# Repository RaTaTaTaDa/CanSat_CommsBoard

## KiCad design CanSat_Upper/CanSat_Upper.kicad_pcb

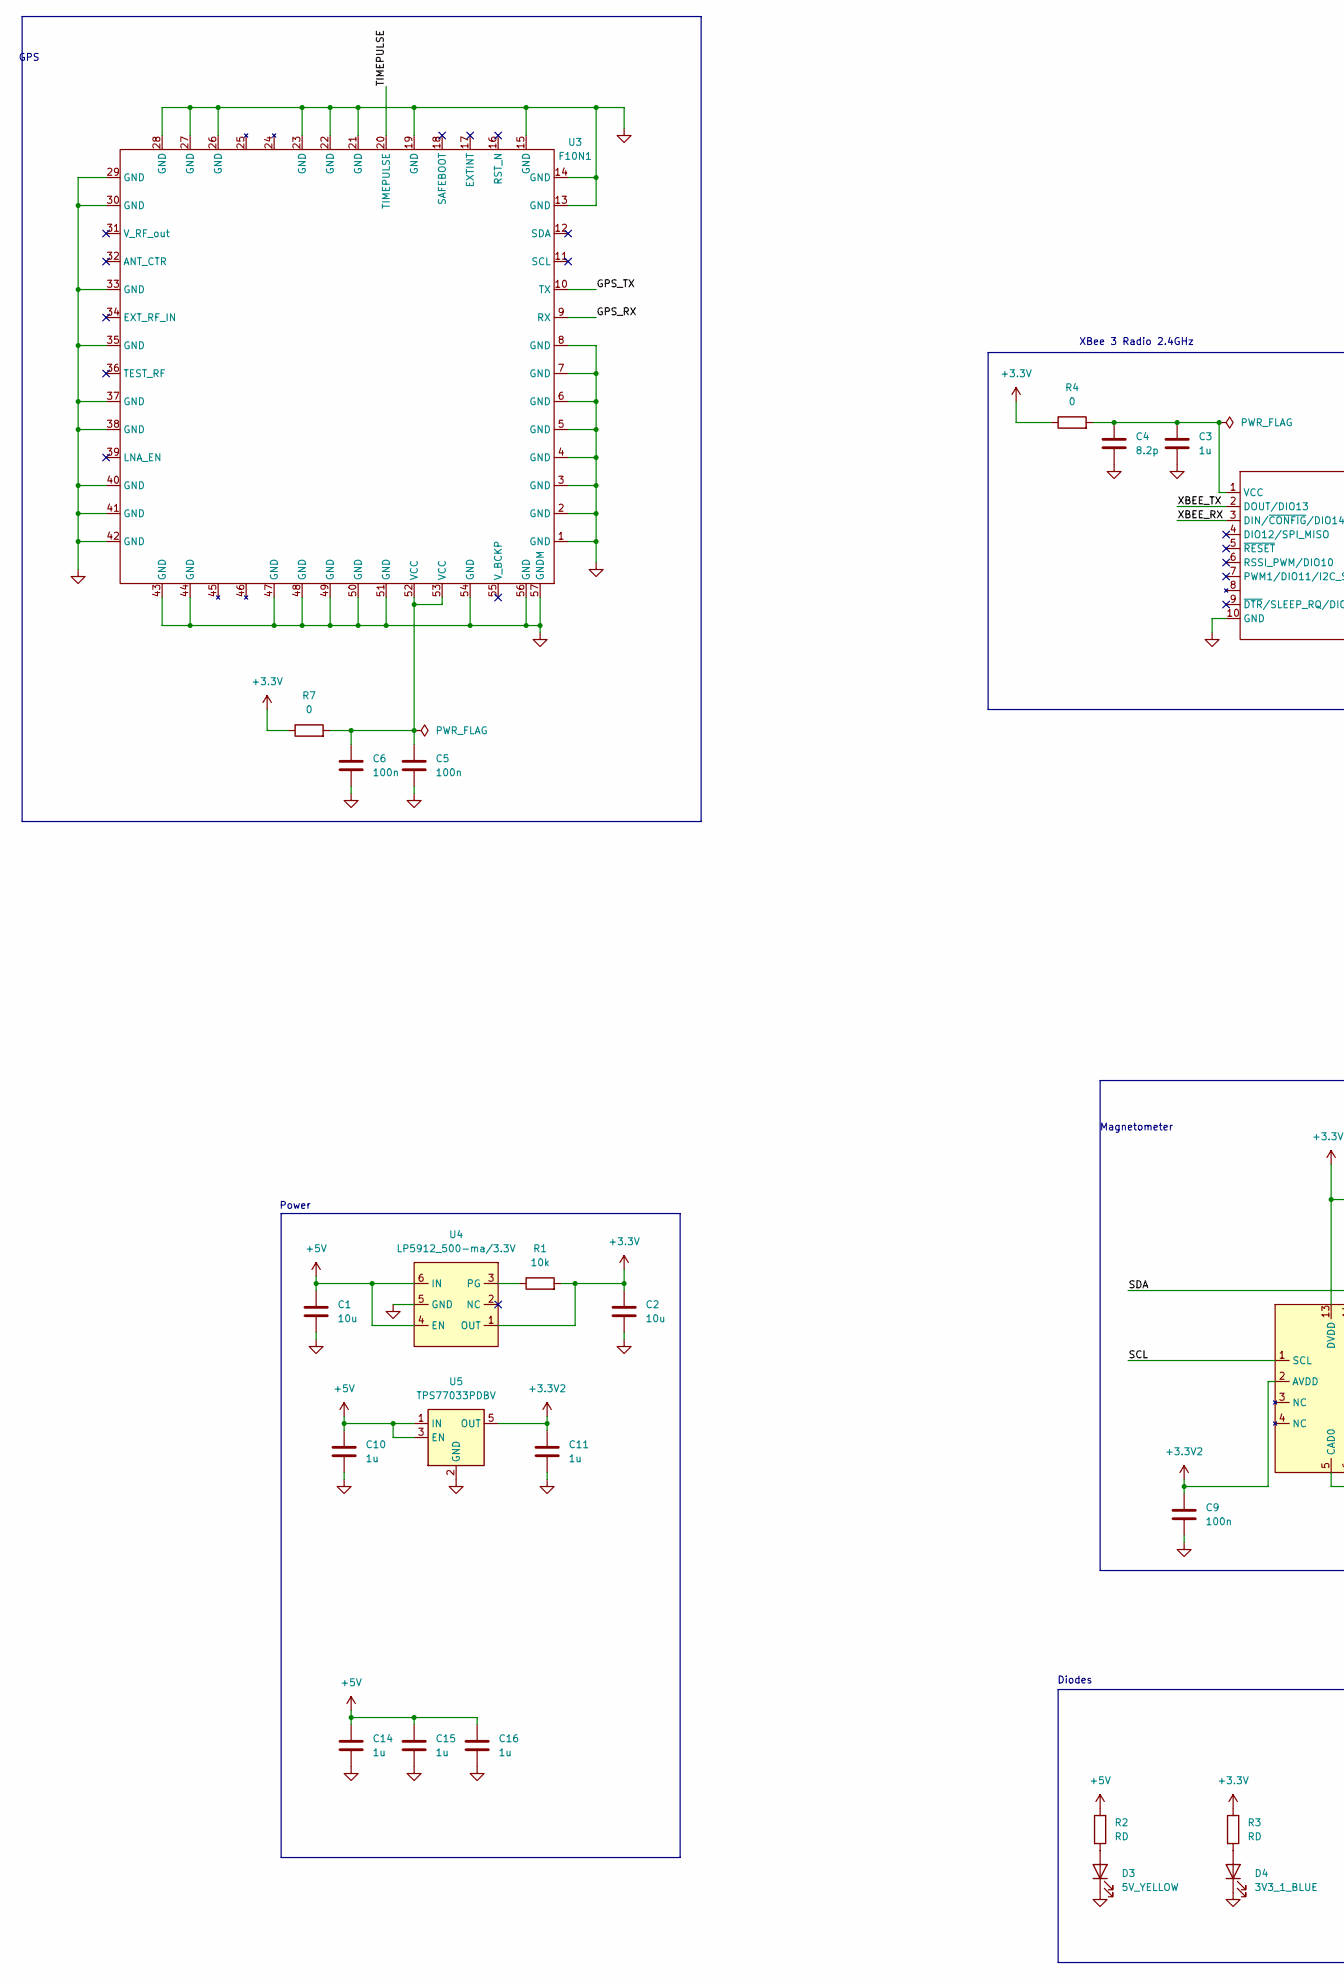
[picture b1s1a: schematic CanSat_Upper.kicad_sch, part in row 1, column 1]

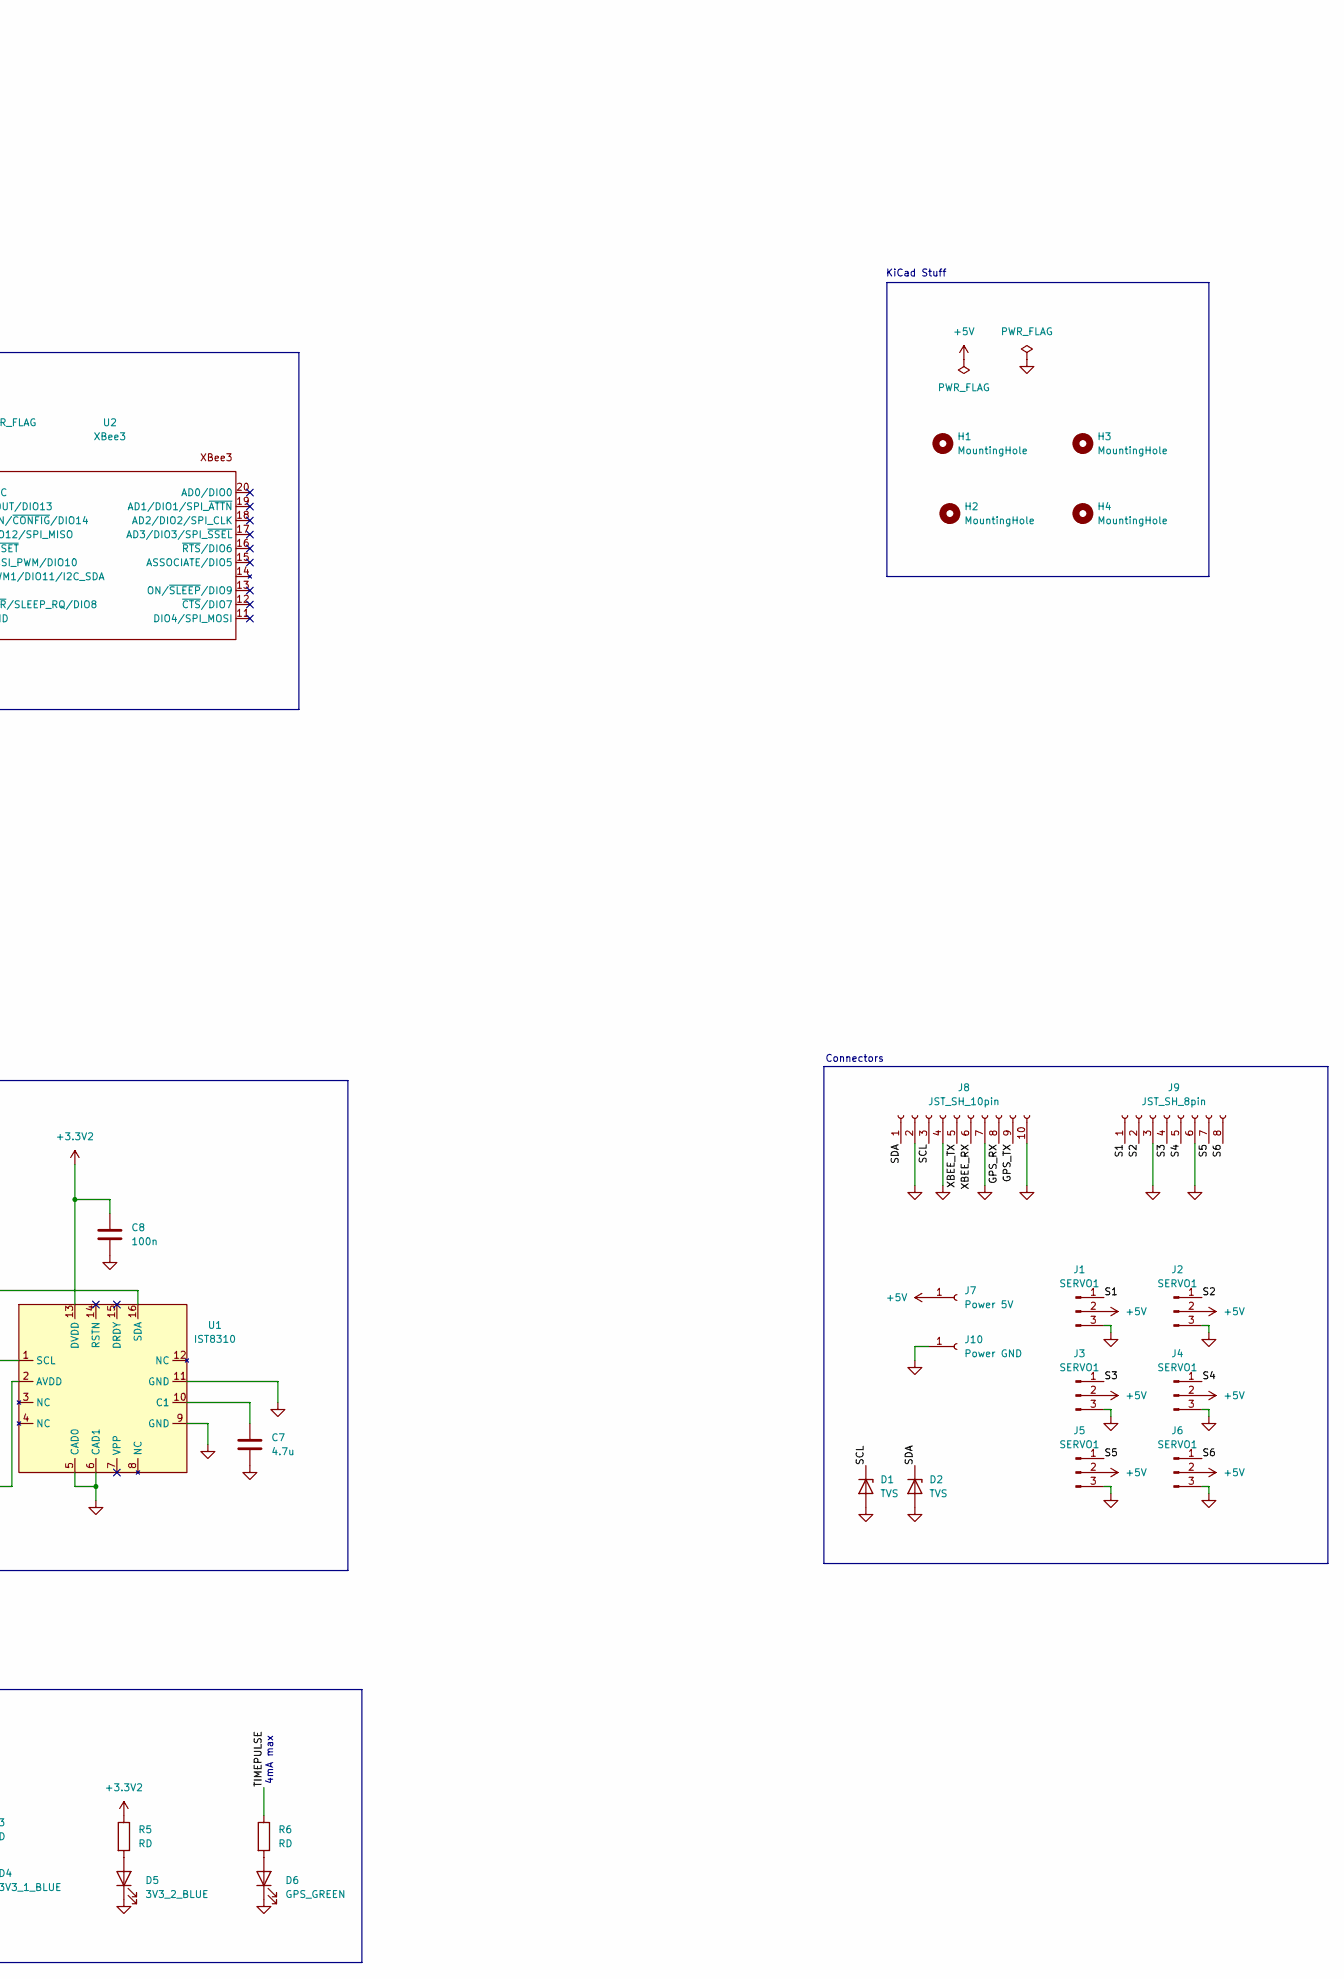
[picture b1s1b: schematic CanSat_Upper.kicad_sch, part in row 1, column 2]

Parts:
C1, C2: 10u; C_0603_1608Metric; LCSC C596327
C3, C10, C11, C14, C15, C16: 1u; C_0603_1608Metric; LCSC C77046
C4: 8.2p; C_0603_1608Metric; LCSC C962145
C5, C6, C8, C9: 100n; C_0603_1608Metric; LCSC C77055
C7: 4.7u; C_0603_1608Metric; LCSC C327022
D1, D2: TVS; D_0402_1005Metric; LCSC C1869319
D3: 5V_YELLOW; D_0805_2012Metric
D4: 3V3_1_BLUE; D_0805_2012Metric
D5: 3V3_2_BLUE; D_0805_2012Metric
D6: GPS_GREEN; D_0805_2012Metric
H1, H2, H3, H4: MountingHole; MountingHole_2mm
J1, J2, J3, J4, J5, J6: SERVO1; PinHeader_1x03_P2.54mm_Vertical; LCSC C265013
J7: Power 5V; SolderWirePad_1x01_SMD_3x6mm
J8: JST_SH_10pin; JST_SH_SM10B-SRSS-TB_1x10-1MP_P1.00mm_Horizontal; LCSC C160409
J9: JST_SH_8pin; JST_SH_SM08B-SRSS-TB_1x08-1MP_P1.00mm_Horizontal; LCSC C160407
J10: Power GND; SolderWirePad_1x01_SMD_3x6mm
R1: 10k; R_0603_1608Metric; LCSC C844918
R2, R3, R5, R6: RD; C_0603_1608Metric
R4, R7: 0; R_0603_1608Metric; LCSC C95177
U1: IST8310; IST8310 LGA; Manufacturer Part Number IST8310; LCSC number C2683055
U2: XBee3
U3: F10N1; ubx_F10
U4: LP5912_500-ma/3.3V; LP5912-LDO; Manufacturer Part Number LP5912-3.3DRVT; LCSC Number C134121
U5: TPS77033PDBV; SOT-23-5; LCSC C36996065

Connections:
+3.3V: C2.1, R1.2, R3.1, R4.1, R7.1, U4.1 (OUT)
+3.3V2: C8.1, C9.1, C11.1, R5.1, U1.2 (AVDD), U1.13 (DVDD), U5.5 (OUT)
+5V: C1.1, C10.1, C14.1, C15.1, C16.1, J1.2, J2.2, J3.2, J4.2, J5.2, J6.2, J7.1, R2.1, U4.4 (EN), U4.6 (IN), U5.1 (IN), U5.3 (EN)
/GPS_RX: J8.8, U3.9 (RX)
/GPS_TX: J8.9, U3.10 (TX)
/S1: J1.1, J9.1
/S2: J2.1, J9.2
/S3: J3.1, J9.4
/S4: J4.1, J9.5
/S5: J5.1, J9.7
/S6: J6.1, J9.8
/SCL: D1.1 (K), J8.3, U1.1 (SCL)
/SDA: D2.1 (K), J8.1, U1.16 (SDA)
/TIMEPULSE: R6.1, U3.20 (TIMEPULSE)
/XBEE_RX: J8.6, U2.3 (DIN/~CONFIG/DIO14)
/XBEE_TX: J8.5, U2.2 (DOUT/DIO13)
GND: C1.2, C2.2, C3.2, C4.2, C5.2, C6.2, C7.2, C8.2, C9.2, C10.2, C11.2, C14.2, C15.2, C16.2, D1.2 (A), D2.2 (A), D3.1 (K), D4.1 (K), D5.1 (K), D6.1 (K), J1.3, J2.3, J3.3, J4.3, J5.3, J6.3, J8.2, J8.4, J8.7, J8.10, J9.3, J9.6, J10.1, U1.5 (CAD0), U1.6 (CAD1), U1.9 (GND), U1.11 (GND), U2.10 (GND), U3.1 (GND), U3.2 (GND), U3.3 (GND), U3.4 (GND), U3.5 (GND), U3.6 (GND), U3.7 (GND), U3.8 (GND), U3.13 (GND), U3.14 (GND), U3.15 (GND), U3.19 (GND), U3.21 (GND), U3.22 (GND), U3.23 (GND), U3.26 (GND), U3.27 (GND), U3.28 (GND), U3.29 (GND), U3.30 (GND), U3.33 (GND), U3.35 (GND), U3.37 (GND), U3.38 (GND), U3.40 (GND), U3.41 (GND), U3.42 (GND), U3.43 (GND), U3.44 (GND), U3.47 (GND), U3.48 (GND), U3.49 (GND), U3.50 (GND), U3.51 (GND), U3.54 (GND), U3.56 (GND), U3.57 (GNDM), U4.5 (GND), U5.2 (GND), U5.4 (GND)
unnamed: C5.1, C6.1, R7.2, U3.52 (VCC), U3.53 (VCC)
unnamed: D3.2 (A), R2.2
unnamed: D4.2 (A), R3.2
unnamed: D5.2 (A), R5.2
unnamed: D6.2 (A), R6.2
unnamed: C7.1, U1.10 (C1)
unnamed: C3.1, C4.1, R4.2, U2.1 (VCC)
unnamed: R1.1, U4.3 (PG)

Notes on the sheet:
GPS
Power
Magnetometer
XBee 3 Radio 2.4GHz
Diodes
KiCad Stuff
4mA max
Connectors

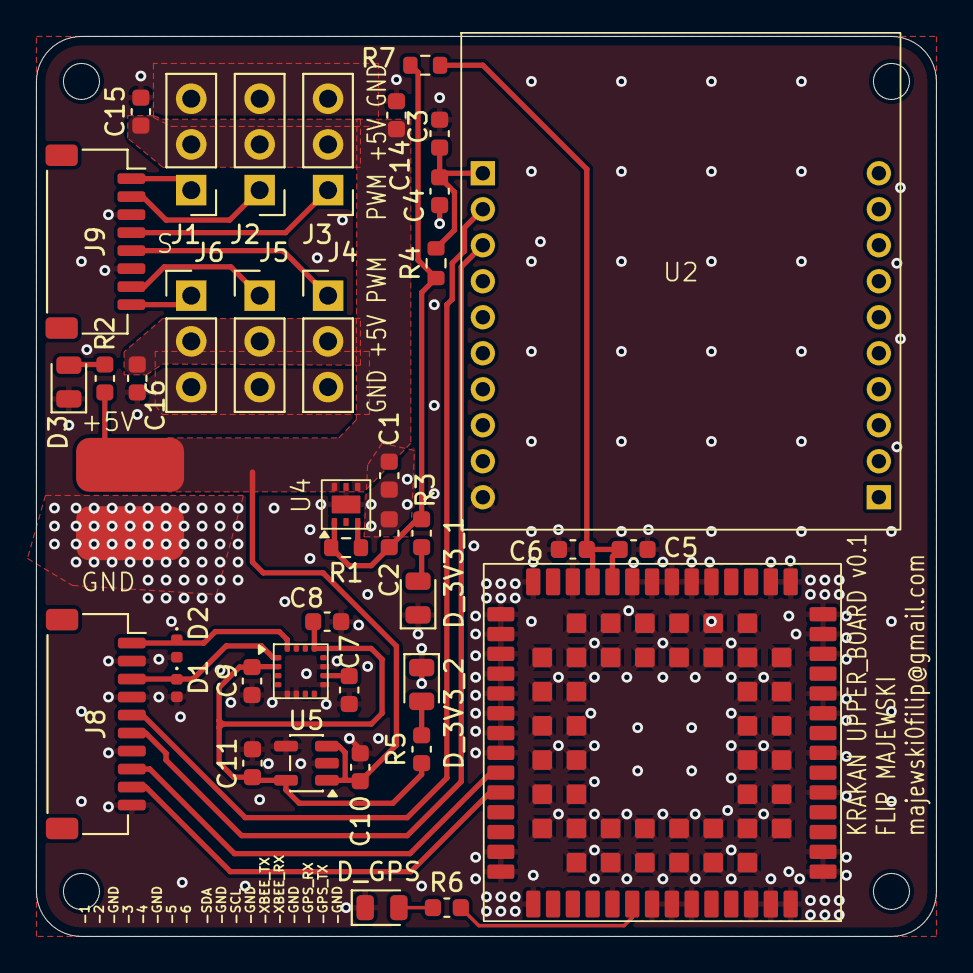
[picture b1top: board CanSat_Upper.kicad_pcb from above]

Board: 2 copper layers, 50.0 x 50.0 mm, 46 parts (0 on the bottom side), 25 nets.

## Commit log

2025-11-23 Components and Libraries added
2025-11-24 Schematic and layout setup finished
2025-11-25 LDO and gps early layout done
2025-11-26 general PBC layout done
2025-11-26 v0.1 finished
2025-11-28 Added variations of the magnetometers power supply
2025-11-29 widened the space between manetometer and ldo
2025-11-30 v0.2 done
2025-11-30 quick fixes to v0.2
2025-11-30 production files done
2025-12-01 small fixes, added 0resistors to turn on/off radio modeules power
2026-03-09 version 1.1 done
